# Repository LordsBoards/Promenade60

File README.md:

# Promenade60
This is a Boardwalk inspired 60% PCB with support for bakeneko mounting :)

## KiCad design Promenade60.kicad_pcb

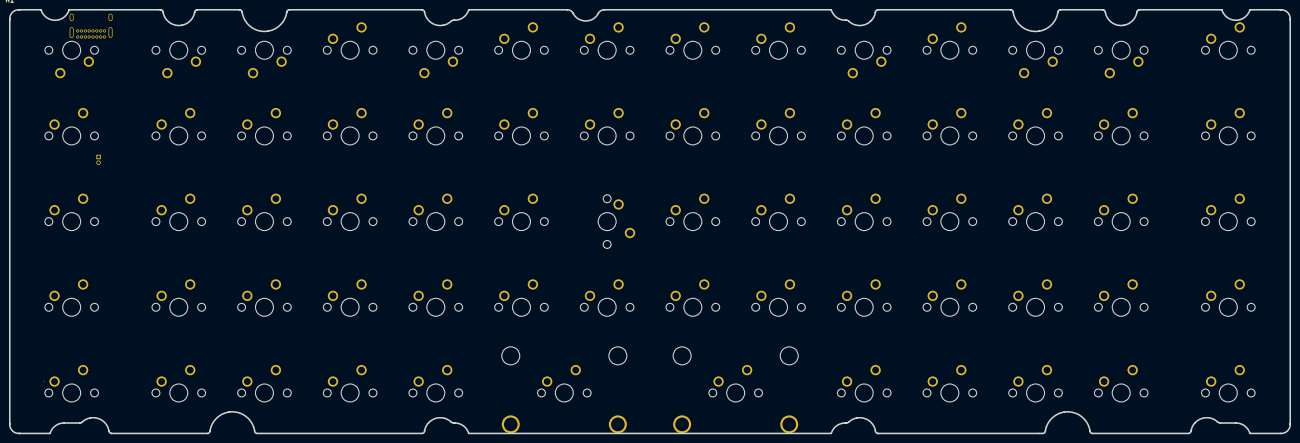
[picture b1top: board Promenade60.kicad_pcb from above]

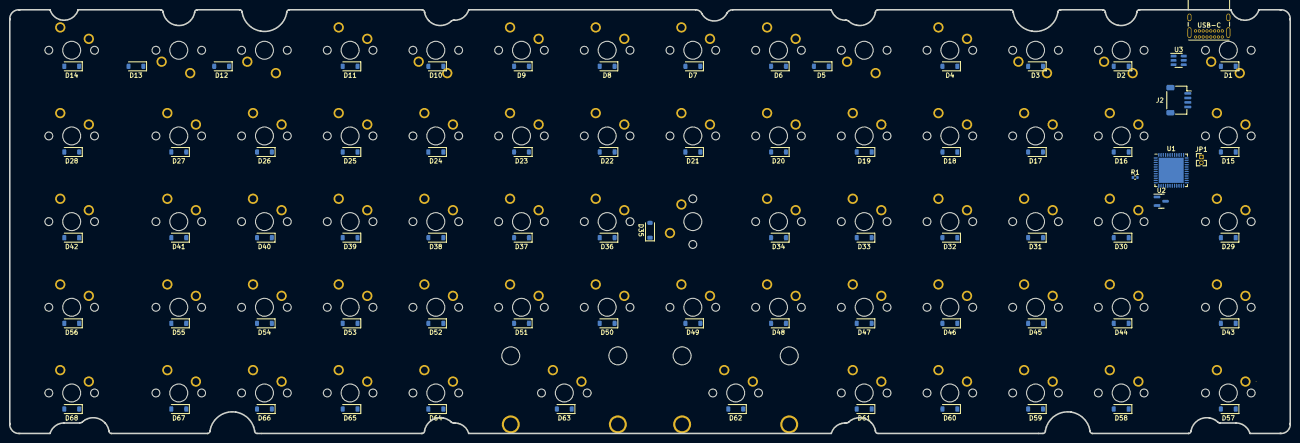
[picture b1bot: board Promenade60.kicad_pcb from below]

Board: 2 copper layers, 284.7 x 94.2 mm, 146 parts (75 on the bottom side), 74 nets.

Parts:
D1, D2, D3, D4, D5, D6, D7, D8, D9, D10, D11, D12, D13, D14, D15, D16, D17, D18, D19, D20, D21, D22, D23, D24, D25, D26, D27, D28, D29, D30, D31, D32, D33, D34, D35, D36, D37, D38, D39, D40, D41, D42, D43, D44, D45, D46, D47, D48, D49, D50, D51, D52, D53, D54, D55, D56, D57, D58, D59, D60, D61, D62, D63, D64, D65, D66, D67, D68: D_Small; D_SOD-123
H1: MountingHole; 60_Percent_Holes
J1: USB_C_Receptacle_GCT_USB4085
J2: SM04B-SRSS; JST_SH_SM04B-SRSS-TB_1x04-1MP_P1.00mm_Horizontal
JP1: Jumper_2_Open; PinHeader_1x02_P1.27mm_Vertical
MX1, MX14, MX15, MX28, MX29, MX42, MX43, MX56, MX57, MX68: Key_None; SW_MX_1.5u
MX2, MX3, MX4, MX5, MX6, MX7, MX8, MX9, MX10, MX11, MX12, MX13, MX16, MX17, MX18, MX19, MX20, MX21, MX22, MX23, MX24, MX25, MX26, MX27, MX30, MX31, MX32, MX33, MX34, MX35, MX36, MX37, MX38, MX39, MX40, MX41, MX44, MX45, MX46, MX47, MX48, MX49, MX50, MX51, MX52, MX53, MX54, MX55, MX58, MX59, MX60, MX61, MX62, MX63, MX64, MX65, MX66, MX67: Key_None; SW_MX_1u
R1: 10k 0402; R_0402_1005Metric
STAB62, STAB63: Stab_None; STAB_MX_P_2u
U1: STM32L443CCUx; QFN-48-1EP_7x7mm_P0.5mm_EP5.6x5.6mm
U2: AP2127N-3.3; SOT-23
U3: USBLC6-2SC6; SOT-23-6

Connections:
+3.3V: JP1.2 (B), U1.1 (VBAT), U1.9 (VDDA), U1.24 (VDD), U1.36 (VDDUSB), U1.48 (VDD), U2.2 (VO)
/DN: J2.2, U1.32 (PA11), U3.3 (I/O2), U3.4 (I/O2)
/DP: J2.3, U1.33 (PA12), U3.1 (I/O1), U3.6 (I/O1)
GND: J2.4, J2.MP (MountPin), R1.2, U1.8 (VSSA), U1.23 (VSS), U1.35 (VSS), U1.47 (VSS), U1.49 (VSS), U2.1 (GND), U3.2 (GND)
unnamed: D1.2 (A), MX1.2
unnamed: D2.2 (A), MX2.2
unnamed: D3.2 (A), MX3.2
unnamed: D4.2 (A), MX4.2
unnamed: D5.2 (A), MX5.2
unnamed: D6.2 (A), MX6.2
unnamed: D7.2 (A), MX7.2
unnamed: D8.2 (A), MX8.2
unnamed: D9.2 (A), MX9.2
unnamed: D10.2 (A), MX10.2
unnamed: D11.2 (A), MX11.2
unnamed: D12.2 (A), MX12.2
unnamed: D13.2 (A), MX13.2
unnamed: D14.2 (A), MX14.2
unnamed: D15.2 (A), MX15.2
unnamed: D16.2 (A), MX16.2
unnamed: D17.2 (A), MX17.2
unnamed: D18.2 (A), MX18.2
unnamed: D19.2 (A), MX19.2
unnamed: D20.2 (A), MX20.2
unnamed: D21.2 (A), MX21.2
unnamed: D22.2 (A), MX22.2
unnamed: D23.2 (A), MX23.2
unnamed: D24.2 (A), MX24.2
unnamed: D25.2 (A), MX25.2
unnamed: D26.2 (A), MX26.2
unnamed: D27.2 (A), MX27.2
unnamed: D28.2 (A), MX28.2
unnamed: D29.2 (A), MX29.2
unnamed: D30.2 (A), MX30.2
unnamed: D31.2 (A), MX31.2
unnamed: D32.2 (A), MX32.2
unnamed: D33.2 (A), MX33.2
unnamed: D34.2 (A), MX34.2
unnamed: D35.2 (A), MX35.2
unnamed: D36.2 (A), MX36.2
unnamed: D37.2 (A), MX37.2
unnamed: D38.2 (A), MX38.2
unnamed: D39.2 (A), MX39.2
unnamed: D40.2 (A), MX40.2
unnamed: D41.2 (A), MX41.2
unnamed: D42.2 (A), MX42.2
unnamed: D43.2 (A), MX43.2
unnamed: D44.2 (A), MX44.2
unnamed: D45.2 (A), MX45.2
unnamed: D46.2 (A), MX46.2
unnamed: D47.2 (A), MX47.2
unnamed: D48.2 (A), MX48.2
unnamed: D49.2 (A), MX49.2
unnamed: D50.2 (A), MX50.2
unnamed: D51.2 (A), MX51.2
unnamed: D52.2 (A), MX52.2
unnamed: D53.2 (A), MX53.2
unnamed: D54.2 (A), MX54.2
unnamed: D55.2 (A), MX55.2
unnamed: D56.2 (A), MX56.2
unnamed: D57.2 (A), MX57.2
unnamed: D58.2 (A), MX58.2
unnamed: D59.2 (A), MX59.2
unnamed: D60.2 (A), MX60.2
unnamed: D61.2 (A), MX61.2
unnamed: D62.2 (A), MX62.2
unnamed: D63.2 (A), MX63.2
unnamed: D64.2 (A), MX64.2
unnamed: D65.2 (A), MX65.2
unnamed: D66.2 (A), MX66.2
unnamed: D67.2 (A), MX67.2
unnamed: D68.2 (A), MX68.2
unnamed: JP1.1 (A), R1.1, U1.44 (PH3)
VBUS: J2.1, U2.3 (VI), U3.5 (VBUS)

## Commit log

2023-08-28 Initial commit.
